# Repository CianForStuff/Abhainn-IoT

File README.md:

Abhainn-IoT is a community centered project to provide a base ia platform in withch a network for river monitoring can be establised on

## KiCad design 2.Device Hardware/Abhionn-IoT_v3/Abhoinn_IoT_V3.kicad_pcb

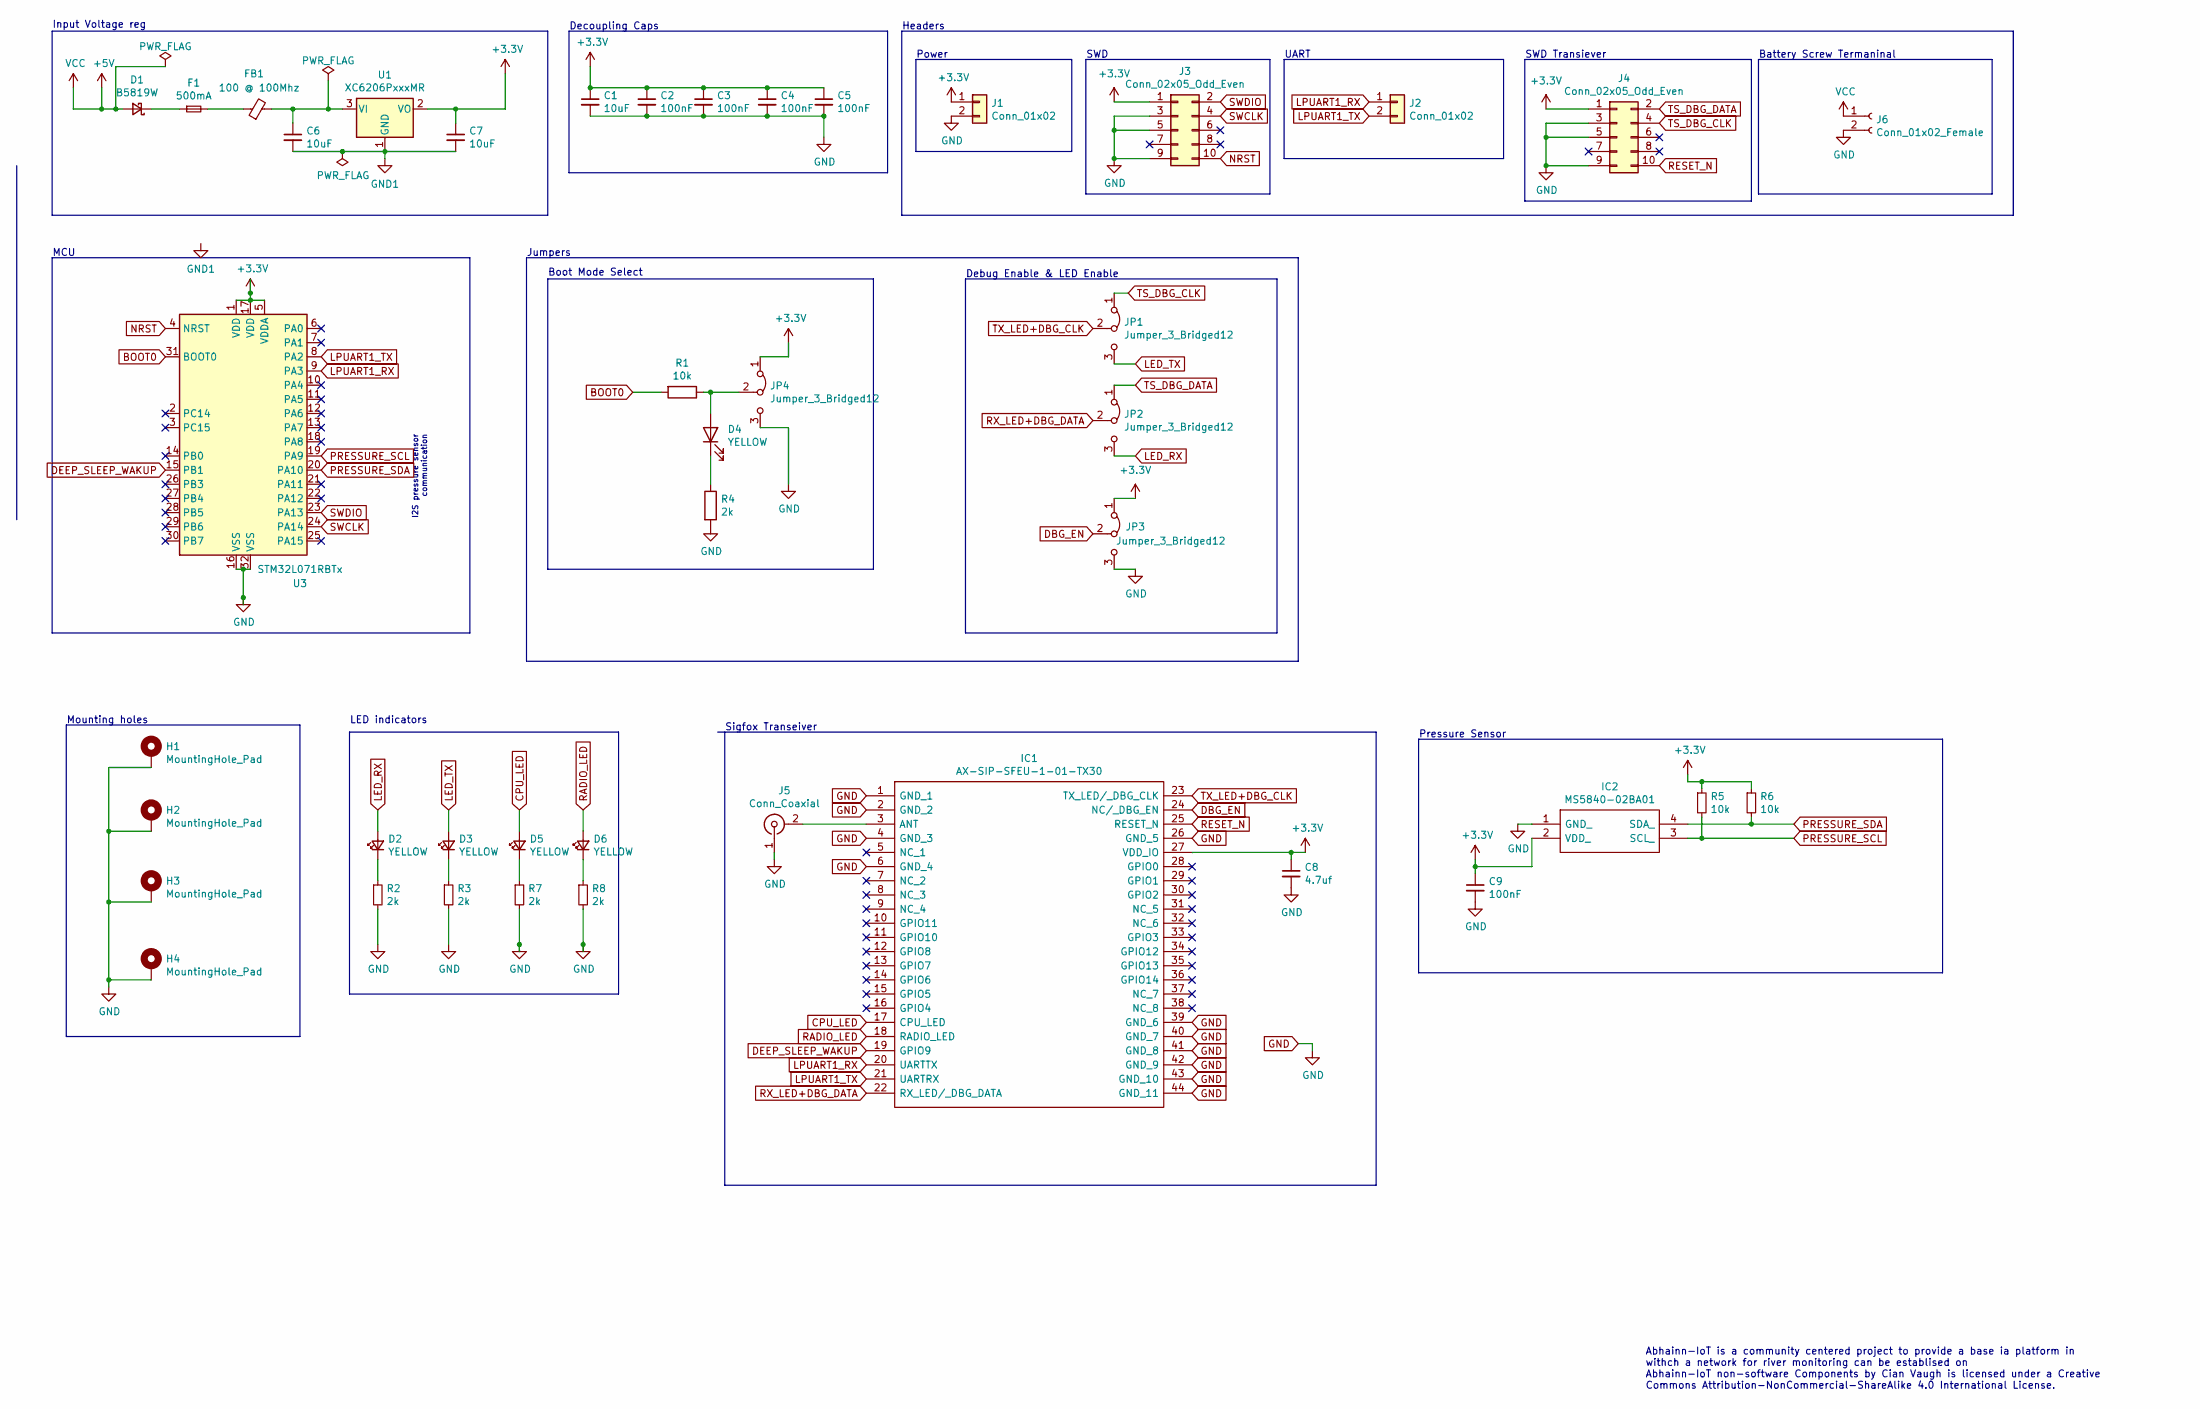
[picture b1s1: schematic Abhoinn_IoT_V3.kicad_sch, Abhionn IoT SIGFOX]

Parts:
C1: 10uF; R_0603_1608Metric_Pad0.98x0.95mm_HandSolder; LCSC Part # C19702
C2, C3, C4, C5, C9: 100nF; C_0603_1608Metric_Pad1.08x0.95mm_HandSolder; LCSC Part # C14663
C6, C7: 10uF; C_0603_1608Metric_Pad1.08x0.95mm_HandSolder; LCSC Part # C19702
C8: 4.7uf; C_0603_1608Metric_Pad1.08x0.95mm_HandSolder; LCSC Part # C19666
D1: B5819W; D_SMA_Handsoldering; LCSC Part # C8598
D2, D3, D4, D5, D6: YELLOW; LED_0805_2012Metric_Castellated; LCSC Part # C2296
F1: 500mA; Fuse_1206_3216Metric_Pad1.42x1.75mm_HandSolder
FB1: 100 @ 100Mhz; L_0603_1608Metric_Pad1.05x0.95mm_HandSolder
H1, H2, H3, H4: MountingHole_Pad; MountingHole_3.2mm_M3_Pad_Via
IC1: AX-SIP-SFEU-1-01-TX30; AXSIPSFEU101TX30; Mouser Part Number 863-AXSIPSFEU101TX30
IC2: MS5840-02BA01; MS584002BA01; Mouser Part Number 824-MS5840-02BA01
J1, J2: Conn_01x02; PinSocket_1x02_P2.54mm_Vertical
J3, J4: Conn_02x05_Odd_Even; PinSocket_2x05_P2.54mm_Vertical
J5: Conn_Coaxial; U.FL_Hirose_U.FL-R-SMT-1_Vertical
J6: Conn_01x02_Female; TerminalBlock_Phoenix_MKDS-1,5-2_1x02_P5.00mm_Horizontal
JP1, JP2, JP3, JP4: Jumper_3_Bridged12; PinSocket_1x03_P2.54mm_Vertical
R1, R5, R6: 10k; R_0805_2012Metric_Pad1.20x1.40mm_HandSolder; LCSC Part # C17414
R2, R3, R4, R7, R8: 2k; R_0805_2012Metric_Pad1.20x1.40mm_HandSolder; LCSC Part # C17604
U1: XC6206PxxxMR; SOT-23; LCSC Part # SOT-23-3L
U3: STM32L071RBTx; LQFP-32_7x7mm_P0.8mm; LCSC Part # C115942

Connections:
+3V3: C1.1, C2.1, C3.1, C4.1, C5.1, C7.1, C8.1, C9.1, IC1.27 (VDD_IO), IC2.2 (VDD_), J1.1, J3.1, J4.1, JP3.1 (A), JP4.1 (A), R5.1, R6.1, U1.2 (VO), U3.1 (VDD), U3.5 (VDDA), U3.17 (VDD)
+5V: D1.2 (A), J6.1
BOOT0: R1.2, U3.31 (BOOT0)
CPU_LED: D5.2 (A), IC1.17 (CPU_LED)
DBG_EN: IC1.24 (NC/_DBG_EN), JP3.2 (C)
DEEP_SLEEP_WAKUP: IC1.19 (GPIO9), U3.15 (PB1)
LED_RX: D2.2 (A), JP2.3 (B)
LED_TX: D3.2 (A), JP1.3 (B)
LPUART1_RX: IC1.20 (UARTTX), J2.1, U3.9 (PA3)
LPUART1_TX: IC1.21 (UARTRX), J2.2, U3.8 (PA2)
NRST: J3.10, U3.4 (NRST)
unnamed: C6.1, FB1.2, U1.3 (VI)
unnamed: D1.1 (K), F1.1
unnamed: D2.1 (K), R2.1
unnamed: D3.1 (K), R3.1
unnamed: D4.1 (K), R4.1
unnamed: D4.2 (A), JP4.2 (C), R1.1
unnamed: D5.1 (K), R7.1
unnamed: D6.1 (K), R8.1
unnamed: F1.2, FB1.1
unnamed: IC1.3 (ANT), J5.2 (Ext)
PRESSURE_SCL: IC2.3 (SCL_), R5.2, U3.19 (PA9)
PRESSURE_SDA: IC2.4 (SDA_), R6.2, U3.20 (PA10)
RADIO_LED: D6.2 (A), IC1.18 (RADIO_LED)
RESET_N: IC1.25 (RESET_N), J4.10
RX_LED+DBG_DATA: IC1.22 (RX_LED/_DBG_DATA), JP2.2 (C)
SWCLK: J3.4, U3.24 (PA14)
SWDIO: J3.2, U3.23 (PA13)
TS_DBG_CLK: J4.4, JP1.1 (A)
TS_DBG_DATA: J4.2, JP2.1 (A)
TX_LED+DBG_CLK: IC1.23 (TX_LED/_DBG_CLK), JP1.2 (C)

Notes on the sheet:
Input Voltage reg
MCU
Mounting holes
LED indicators
I2S pressure sensor communication
Jumpers
Boot Mode Select
Decoupling Caps
Sigfox Transeiver
Headers
Power
Debug Enable & LED Enable
SWD
UART
Pressure Sensor
SWD Transiever
Abhainn-IoT is a community centered project to provide a base ia platform in withch a network for river monitoring can be establised on Abhainn-IoT non-software Components by Cian Vaugh is licensed under a Creative Commons Attribution-NonCommercial-ShareAlike 4.0 International License.
Battery Screw Termaninal

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
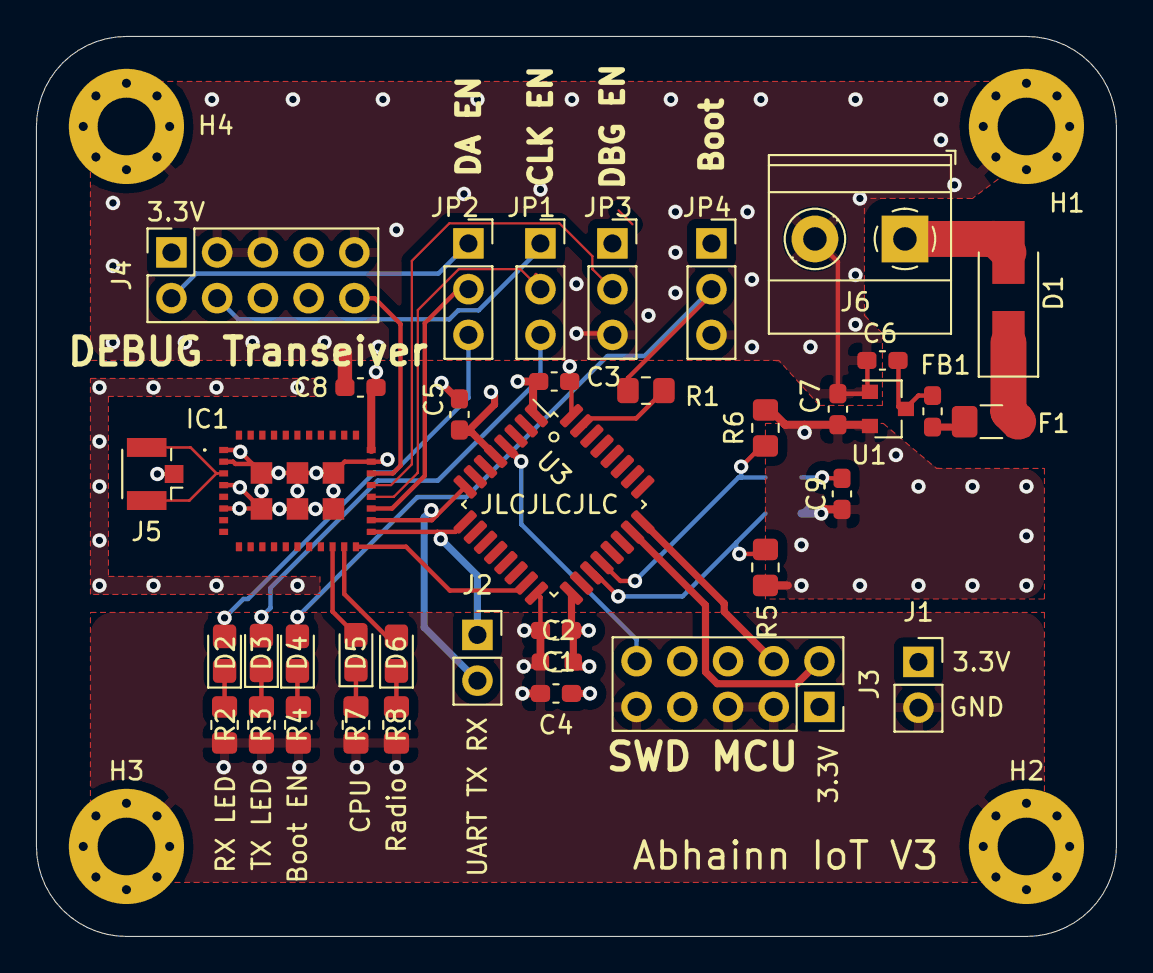
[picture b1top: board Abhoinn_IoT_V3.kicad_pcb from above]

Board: 4 copper layers, 60.0 x 50.0 mm, 43 parts (1 on the bottom side), 32 nets.

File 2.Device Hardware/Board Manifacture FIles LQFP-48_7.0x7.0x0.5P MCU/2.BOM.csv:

Comment,Designator,Footprint,LCSC
"10uF","C1","Resistor_SMD:R_0603_1608Metric_Pad0.98x0.95mm_HandSolder",""
"10uF","C6,C7","Capacitor_SMD:C_0603_1608Metric_Pad1.08x0.95mm_HandSolder",""
"4.7uf","C8","Capacitor_SMD:C_0603_1608Metric_Pad1.08x0.95mm_HandSolder",""
"100nF","C2,C3,C4,C5,C9","Capacitor_SMD:C_0603_1608Metric_Pad1.08x0.95mm_HandSolder",""
"B5819W","D1","Diode_SMD:D_SMA_Handsoldering",""
"YELLOW","D2,D3,D4,D5,D6","LED_SMD:LED_0805_2012Metric_Castellated",""
"500mA","F1","Fuse:Fuse_1206_3216Metric_Pad1.42x1.75mm_HandSolder",""
"100 @ 100Mhz","FB1","Inductor_SMD:L_0603_1608Metric_Pad1.05x0.95mm_HandSolder",""
"MountingHole_Pad","H1,H2,H3,H4","MountingHole:MountingHole_3.2mm_M3_Pad_Via",""
"AX-SIP-SFEU-1-01-TX30","IC1","AXSIPSFEU101TX30",""
"MS5840-02BA01","IC2","MS584002BA01",""
"Conn_01x02","J1,J2","Connector_PinSocket_2.54mm:PinSocket_1x02_P2.54mm_Vertical",""
"Conn_02x05_Odd_Even","J3,J4","Connector_PinSocket_2.54mm:PinSocket_2x05_P2.54mm_Vertical",""
"Conn_Coaxial","J5","Connector_Coaxial:U.FL_Hirose_U.FL-R-SMT-1_Vertical",""
"Conn_01x02_Female","J6","TerminalBlock_Phoenix:TerminalBlock_Phoenix_MKDS-1,5-2_1x02_P5.00mm_Horizontal",""
"Jumper_3_Bridged12","JP1,JP2,JP3,JP4","Connector_PinSocket_2.54mm:PinSocket_1x03_P2.54mm_Vertical",""
"10k","R1,R5,R6","Resistor_SMD:R_0805_2012Metric_Pad1.20x1.40mm_HandSolder",""
"2k","R2,R3,R4,R7,R8","Resistor_SMD:R_0805_2012Metric_Pad1.20x1.40mm_HandSolder",""
"XC6206PxxxMR","U1","Package_TO_SOT_SMD:SOT-23",""
"STM32L071RBTx","U3","Package_QFP:LQFP-32_7x7mm_P0.8mm",""

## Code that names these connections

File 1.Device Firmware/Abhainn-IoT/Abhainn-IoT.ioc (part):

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PA10.Mode=I2C
Mcu.UserName=STM32L031K6Tx
PA9.GPIO_Label=PRESSURE_SCL
PA9.GPIOParameters=GPIO_Label
PA3.Mode=Multiprocessor_communication
PA13.Signal=SYS_SWDIO
PA9.Mode=I2C
PA9.Signal=I2C1_SCL
RCC.HSE_VALUE=8000000
board=custom
PA14.Mode=Serial_Wire
PA10.GPIOParameters=GPIO_Label
PA10.GPIO_Label=PRESSURE_SDA
PA13.Mode=Serial_Wire
Mcu.Name=STM32L031K(4-6)Tx
PA2.Signal=LPUART1_TX
RCC.SYSCLKFreq_VALUE=2097000
Mcu.Package=LQFP32
PA10.Signal=I2C1_SDA
PA14.Signal=SYS_SWCLK
PA2.Mode=Multiprocessor_communication
PA3.Signal=LPUART1_RX

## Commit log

2021-06-22 Working Docuemntents
    working documents, not yet complete
2021-06-28 FIle orginisation
2021-06-28 uplode images
2021-06-28 Add image
2021-06-28 fix image
2021-06-28 rename image
2021-06-28 Informatuion on the Project
2021-06-28 Project Information
2021-07-03 initial Clean Up
2021-07-04 Updated PCB and SCH
    Updated PCB and SCH to add USB interface
2021-07-04 PCB updates
2021-07-04 format SCH, Create PDF
2021-07-04 SCH png
2021-07-04 update PCB
2021-07-14 add bom
2021-07-16 v2 final and production files
2021-07-27 Updatre fuese
    Supply issure, footprint swap for 500mA fuse
2021-07-27 minor update
2021-08-11 Initial Comitte
2021-08-11 update symbols
2021-08-11 Update Drawing
2021-08-11 Add colour scheamatic
2021-08-11 update names
2021-08-11 Update image address
2021-08-11 update image
2021-08-23 Final Rev layout, Add build Files
2021-08-23 Update Dir Layout
2021-09-16 Add layout for 48 pin MCU
2021-09-25 Firmware initial draft
    Firmware initial draft still work to do
2021-09-27 Formating
2021-09-27 Folder structure
2021-09-27 Create folder structure
2021-09-27 update read me
